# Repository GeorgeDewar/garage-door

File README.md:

# garage-door

ESP8266-based garage door controller (status and control via MQTT)

This is a personal project to control my garage door opener remotely using my phone. It's designed specifically around my garage door opener, which is pretty old and I'm not even sure what make and model it is. It comprises a circuit containing a NodeMCU ESP8266 dev board, some components, and a small modification to the door opener to expose additional signals.

My opener has a series of screw terminals, notably:

- GND - common ground for all other terminals
- P/B (push button) - a 5V signal that when pulled low, causes the door to open or close. I believe it is equivalent to the button on the side of the unit
- 15V - a supply of power, which is poorly regulated so is often more like 18-20V

I had two goals. Firstly, to install a button inside the house with an LED that shows the status of the door.  For that I used the [PDL 680TMNPB-WH](https://www.scottelectrical.co.nz/shop/switch-gear-wiring-devices/modulesmechs/specialty/pdl-switch-elv-tactile-red-neon/) which combines a momentary switch (button) with an LED. But the LED has a built-in resistor such that it is designed to take a 24V input, which means I can't drive it easily from a microcontroller. So, I elected to use the 15V supply to power the LED. In fact, even with 5V the LED is visible, but dim. 15-20V is good and bright.

The LED is on when the door is open, flashing when it is partially open (e.g. opening or closing), and off when it is closed. The button is connected directly (electrically speaking) to the P/B terminal on the garage door so that it will work even if my device is unpowered.

The second goal is to control it from my phone. That means being able to see the status, and actuate the door. To achieve this, I made the microcontroller send to Home Assistant via MQTT status updates, and accept commands, which cause it to pull the P/B signal low to simulate a button press.

The list of terminals I gave above did not include any terminal which can be used to detect the state of the door. But the opener does have two microswitches that are actuated by cams to tell it when it has fully closed or fully opened. These are also 5V signals that are pulled low by the microswitches. I tapped into these and exposed them, along with the other three termials, on a convenient DB9 socket which I mounted on the opener. Using these two signals, my microcontroller can tell if the door is open, closed, or partially open. The fourth state, where both signals are low, should never occur.

This repository contains the firmware for the ESP8266, and the circuit diagram and veroboard layout I used. I designed in support for end-user WiFi setup, but unfortunately the MQTT settings are hard-coded. I don't know if I will ever bother to change that since I am not highly likely to have additional users to support, and if I do get some, they can just change the code.

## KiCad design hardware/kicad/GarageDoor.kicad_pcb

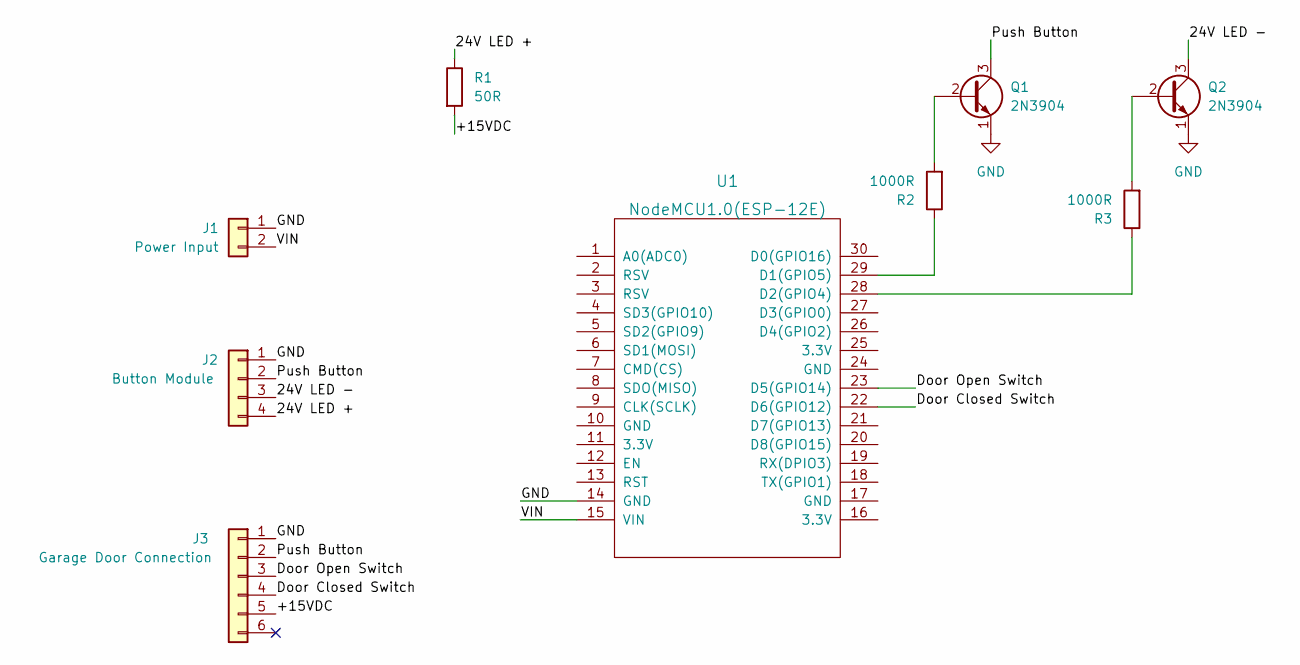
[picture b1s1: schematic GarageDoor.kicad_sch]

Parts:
J1: Power Input; PinHeader_1x02_P2.54mm_Vertical
J2: Button Module; PinHeader_1x04_P2.54mm_Vertical
J3: Garage Door Connection; PinHeader_1x06_P2.54mm_Vertical
Q1, Q2: 2N3904; TO-92_Inline
R1: 50R; R_Bare_Metal_Element_L16.3mm_W4.8mm_P15.30mm
R2, R3: 1000R; R_Bare_Metal_Element_L16.3mm_W4.8mm_P15.30mm
U1: NodeMCU1.0(ESP-12E); NodeMCU1.0(12-E)

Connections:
/24V LED +: J2.4, R1.1
/24V LED -: J2.3, Q2.3 (C)
/+15VDC: J3.5, R1.2
/Door Closed Switch: J3.4, U1.22 (D6(GPIO12))
/Door Open Switch: J3.3, U1.23 (D5(GPIO14))
/Push Button: J2.2, J3.2, Q1.3 (C)
/VIN: J1.2, U1.15 (VIN)
GND: J1.1, J2.1, J3.1, Q1.1 (E), Q2.1 (E), U1.14 (GND)
unnamed: Q1.2 (B), R2.2
unnamed: Q2.2 (B), R3.2
unnamed: R3.1, U1.28 (D2(GPIO4))
unnamed: R2.1, U1.29 (D1(GPIO5))

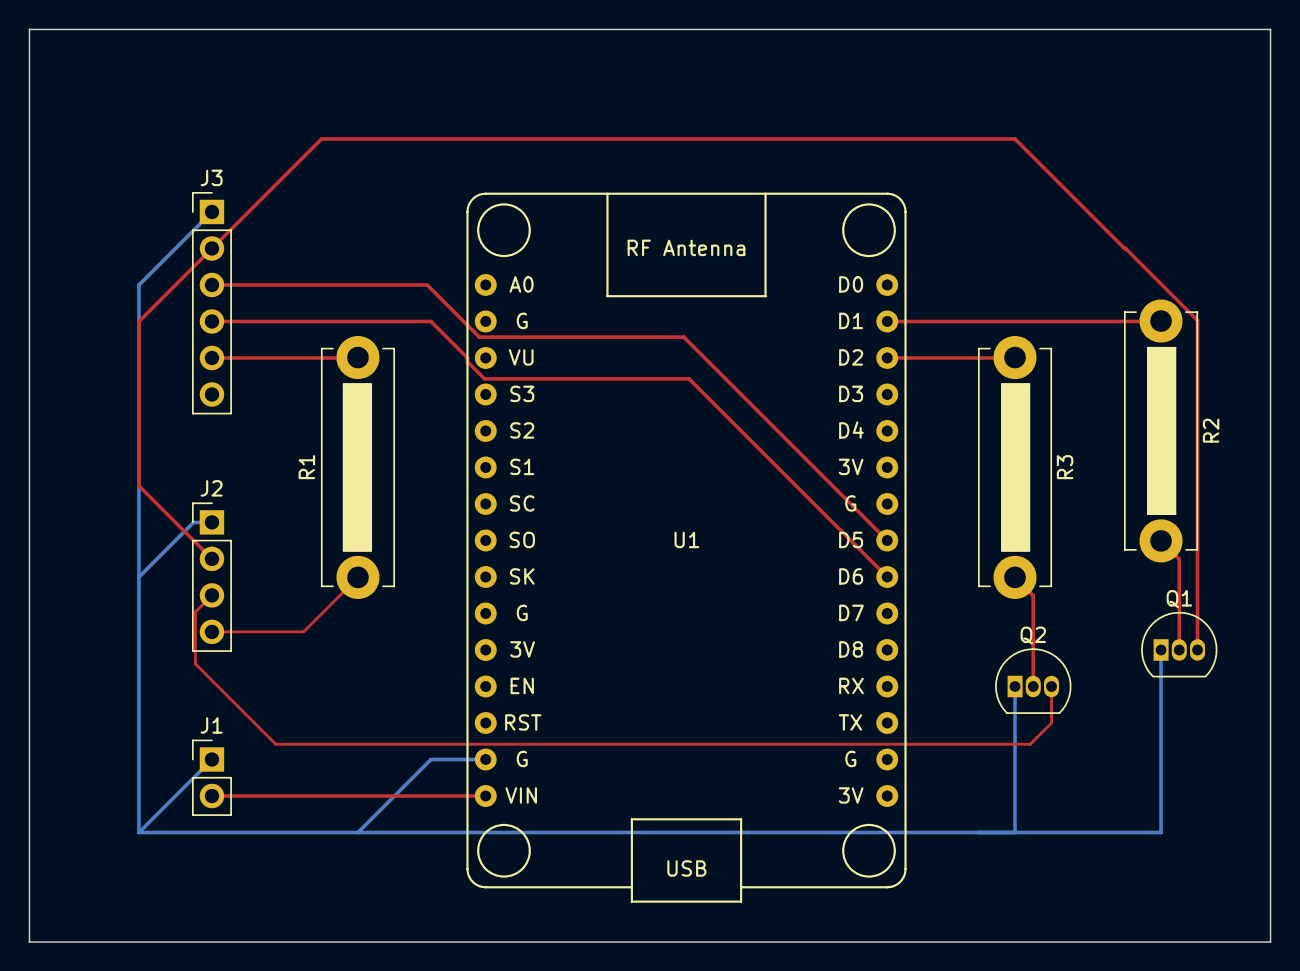
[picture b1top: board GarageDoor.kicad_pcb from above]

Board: 2 copper layers, 86.4 x 63.5 mm, 9 parts (0 on the bottom side), 12 nets.

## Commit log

2022-09-13 Different library
2022-09-14 MQTT, drive transistor
2022-09-23 Add code - just starting
2022-09-23 Work on the firmware a bit
2022-09-24 Tweaks
2022-09-24 Logic to send status
2022-09-24 Better simpler logic
2022-09-26 Get LED output working right
2022-09-26 Remove old Arduino IDE based version
2022-09-27 Add Kicad files
2022-09-27 Add veroboard layout
2022-09-28 Hopefully make it work better when WiFi/MQTT is unavailable
2022-09-28 Tidy up code
